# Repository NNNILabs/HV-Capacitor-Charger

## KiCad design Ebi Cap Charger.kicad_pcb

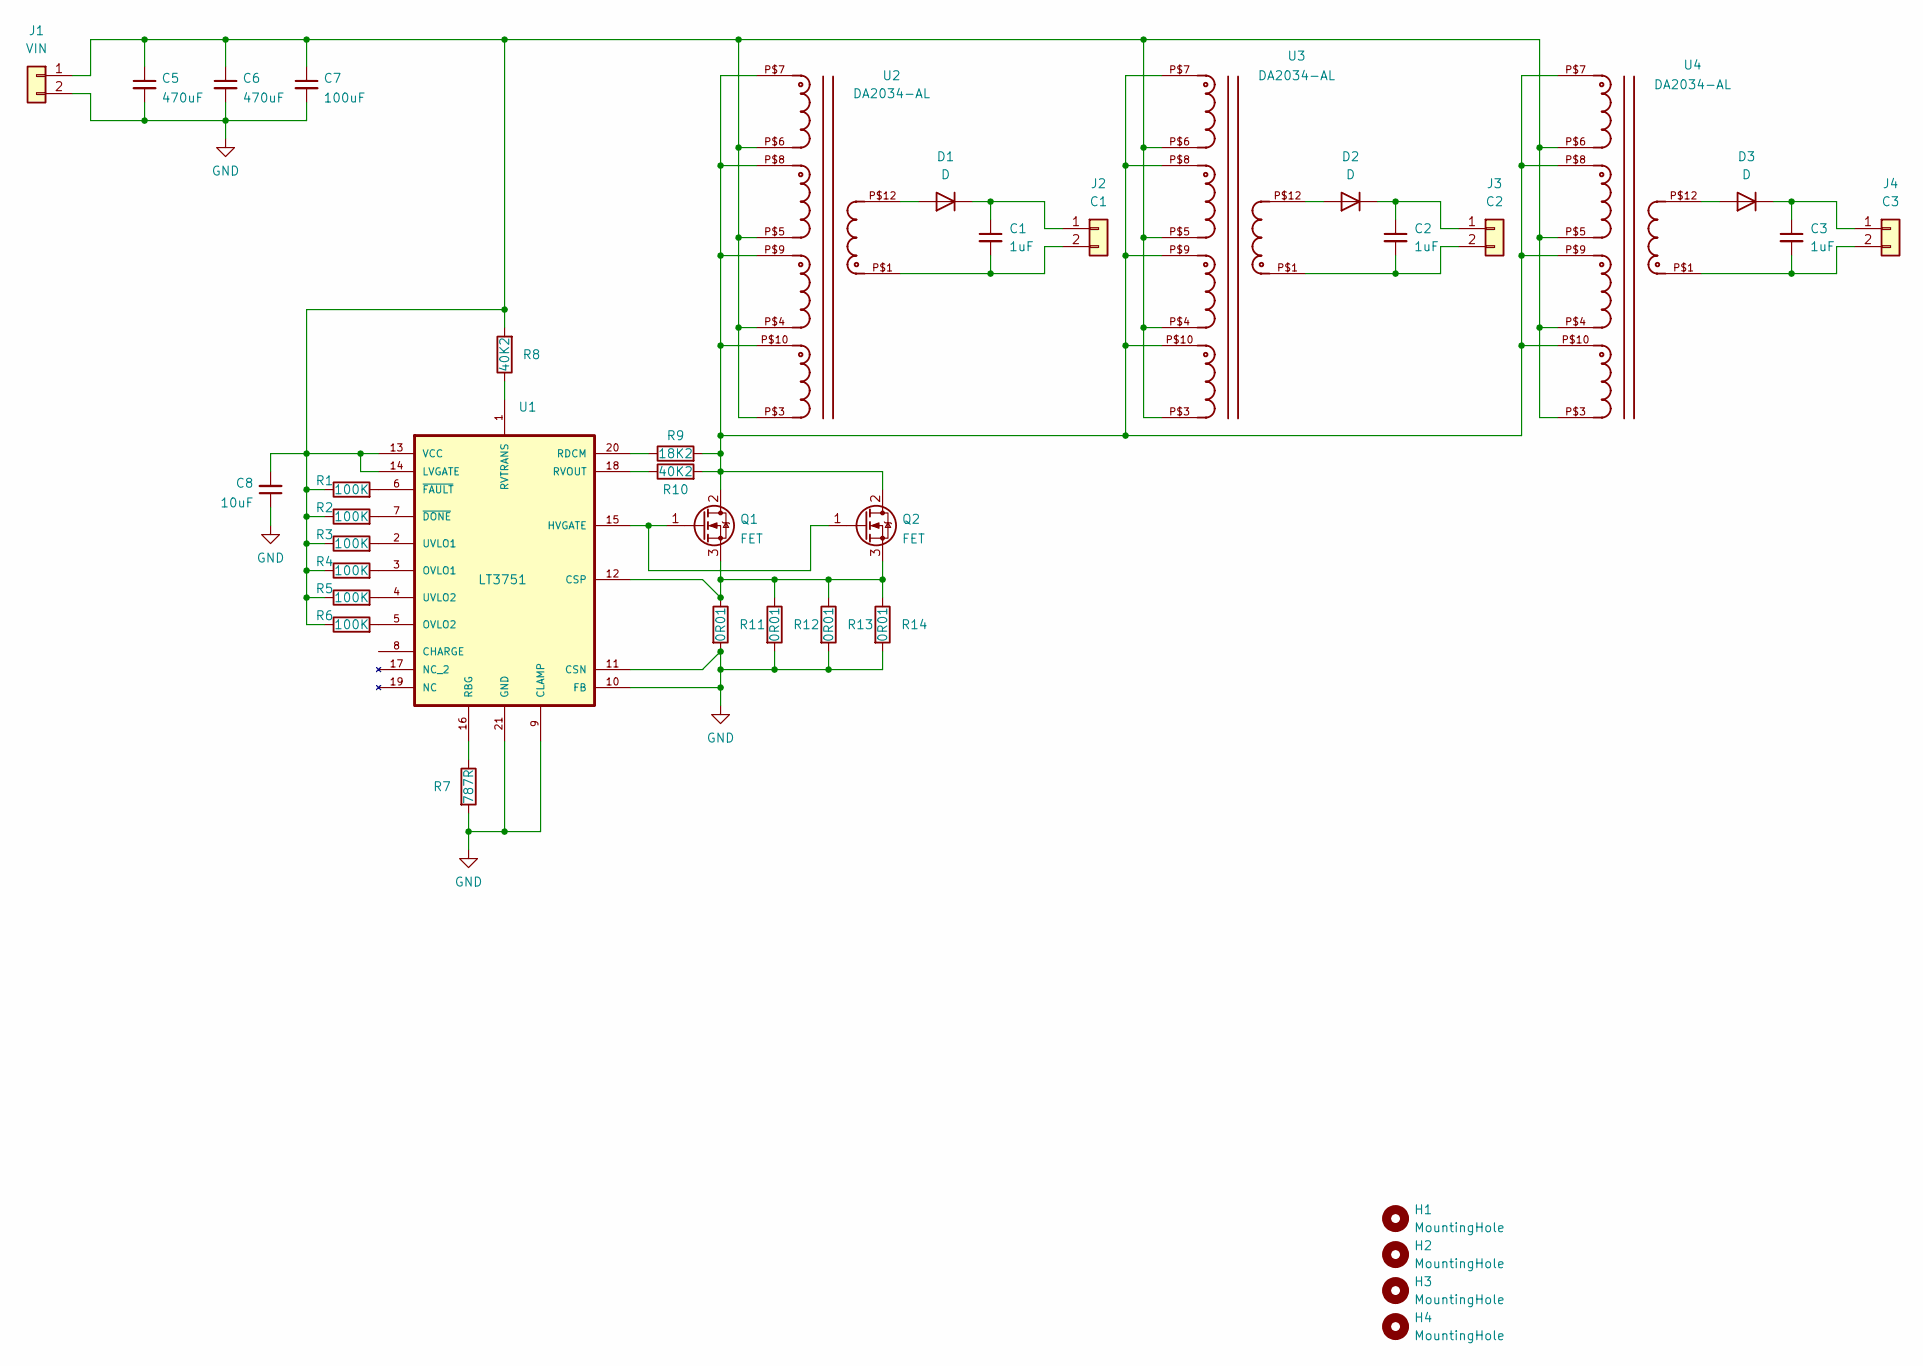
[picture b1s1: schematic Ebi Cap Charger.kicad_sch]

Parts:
C1, C2, C3: 1uF; C_1206_3216Metric
C5, C6: 470uF; CP_Radial_D10.0mm_P5.00mm
C7: 100uF; C_2220_5650Metric
C8: 10uF; C_0603_1608Metric
D1, D2, D3: D; D_SMB
H1, H2, H3, H4: MountingHole; MountingHole_3.2mm_M3_Pad_Via
J1: VIN; PinHeader_1x02_P2.54mm_Vertical
J2: C1; PinHeader_1x02_P2.54mm_Vertical
J3: C2; PinHeader_1x02_P2.54mm_Vertical
J4: C3; PinHeader_1x02_P2.54mm_Vertical
Q1, Q2: FET; TO-252-2
R1, R2, R3, R4, R5, R6: 100K; R_0603_1608Metric
R7: 787R; R_0603_1608Metric
R8, R10: 40K2; R_0603_1608Metric
R9: 18K2; R_0603_1608Metric
R11, R12, R13, R14: 0R01; R_2512_6332Metric
U1: LT3751; HTSSOP-20-1EP_4.4x6.5mm_P0.65mm_EP2.74x3.86mm; MPN LT3751IFE#PBF
U2, U3, U4: DA2034-AL

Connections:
GND: C5.2, C6.2, C7.2, C8.1, J1.2, R7.2, R11.2, R12.2, R13.2, R14.2, U1.9 (CLAMP), U1.10 (FB), U1.11 (CSN), U1.21 (GND)
unnamed: C1.1, D1.1 (K), J2.1
unnamed: C1.2, J2.2, U2.P$1
unnamed: C2.1, D2.1 (K), J3.1
unnamed: C2.2, J3.2, U3.P$1
unnamed: C3.1, D3.1 (K), J4.1
unnamed: C3.2, J4.2, U4.P$1
unnamed: C5.1, C6.1, C7.1, C8.2, J1.1, R1.1, R2.1, R3.1, R4.1, R5.1, R6.1, R8.2, U1.13 (VCC), U1.14 (LVGATE), U2.P$3, U2.P$4, U2.P$5, U2.P$6, U3.P$3, U3.P$4, U3.P$5, U3.P$6, U4.P$3, U4.P$4, U4.P$5, U4.P$6
unnamed: D1.2 (A), U2.P$12
unnamed: D2.2 (A), U3.P$12
unnamed: D3.2 (A), U4.P$12
unnamed: Q1.1 (G), Q2.1 (G), U1.15 (HVGATE)
unnamed: Q1.2 (D), Q2.2 (D), R9.2, R10.2, U2.P$7, U2.P$8, U2.P$9, U2.P$10, U3.P$7, U3.P$8, U3.P$9, U3.P$10, U4.P$7, U4.P$8, U4.P$9, U4.P$10
unnamed: Q1.3 (S), Q2.3 (S), R11.1, R12.1, R13.1, R14.1, U1.12 (CSP)
unnamed: R1.2, U1.6 (~FAULT)
unnamed: R2.2, U1.7 (~DONE)
unnamed: R3.2, U1.2 (UVLO1)
unnamed: R4.2, U1.3 (OVLO1)
unnamed: R5.2, U1.4 (UVLO2)
unnamed: R6.2, U1.5 (OVLO2)
unnamed: R7.1, U1.16 (RBG)
unnamed: R8.1, U1.1 (RVTRANS)
unnamed: R9.1, U1.20 (RDCM)
unnamed: R10.1, U1.18 (RVOUT)

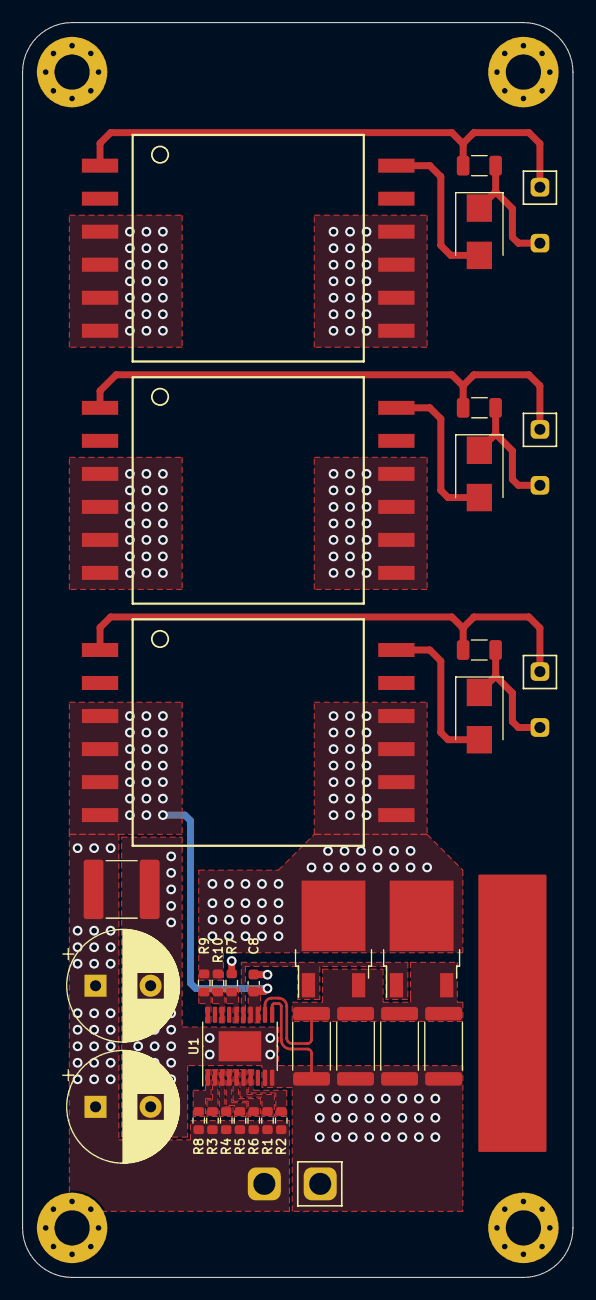
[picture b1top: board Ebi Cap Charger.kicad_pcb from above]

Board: 2 copper layers, 50.0 x 114.0 mm, 38 parts (0 on the bottom side), 24 nets.

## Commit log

2022-08-28 Started schematic
2022-09-01 updated PCB
2022-09-19 PCB draft
